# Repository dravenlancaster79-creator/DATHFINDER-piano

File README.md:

# DATHFINDER-piano
very simple begginer PCB that is a out of tune piano, with four different buttons having a different tone! i built this
 because i wanted to learn hoe PCBs work and operate, so far ive learned many new skills including Kcad and Cpp!!

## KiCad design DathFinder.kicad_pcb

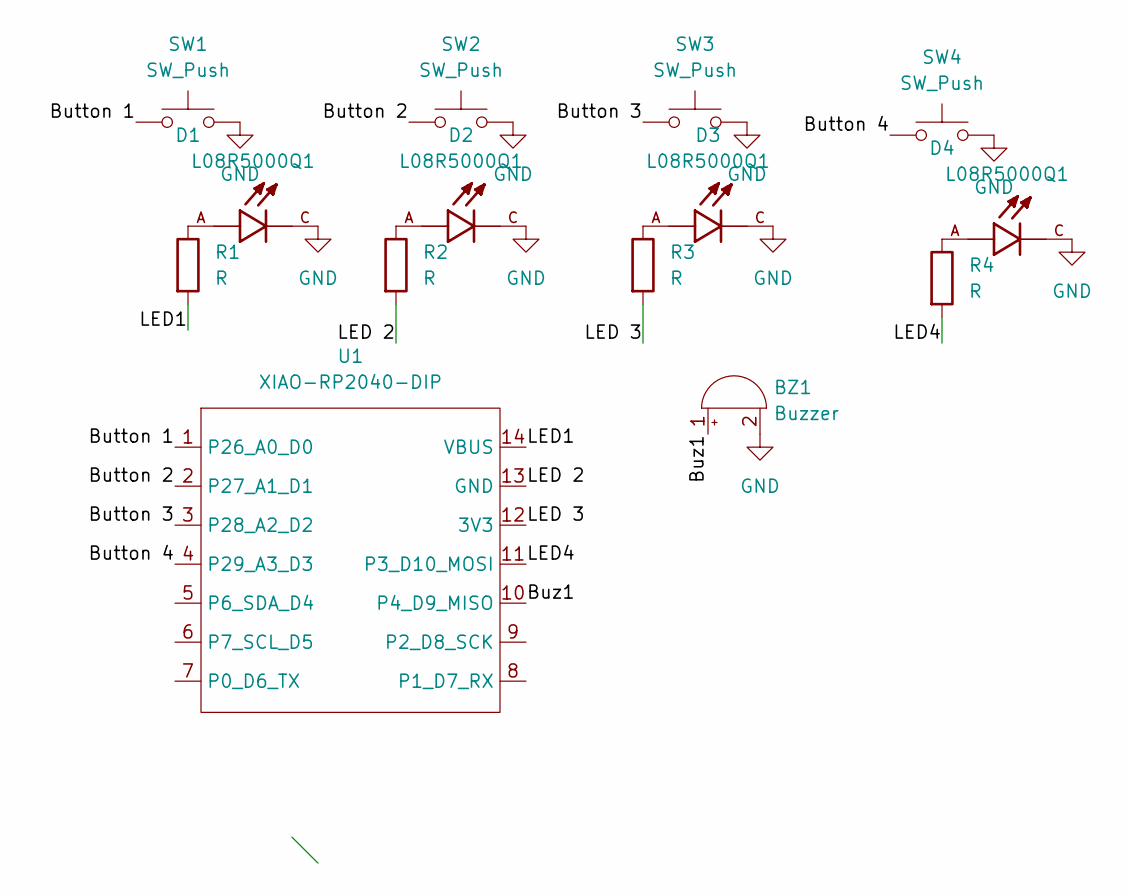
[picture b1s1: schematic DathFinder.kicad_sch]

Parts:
BZ1: Buzzer; Buzzer_D14mm_H7mm_P10mm
D1, D2, D3, D4: L08R5000Q1; LEDRD254W57D500H1070; PARTREV NA
R1, R2, R3, R4: R; R_Axial_DIN0204_L3.6mm_D1.6mm_P5.08mm_Horizontal
SW1, SW2, SW3, SW4: SW_Push; SW_Cherry_MX_1.00u_Plate
U1: XIAO-RP2040-DIP

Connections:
/Button 1: SW1.1, U1.1 (P26_A0_D0)
/Button 2: SW2.1, U1.2 (P27_A1_D1)
/Button 3: SW3.1, U1.3 (P28_A2_D2)
/Button 4: SW4.1, U1.4 (P29_A3_D3)
/Buz1: BZ1.1 (+), U1.10 (P4_D9_MISO)
/LED1: R1.2, U1.14 (VBUS)
/LED4: R4.2, U1.11 (P3_D10_MOSI)
/LED 2: R2.2, U1.13 (GND)
/LED 3: R3.2, U1.12 (3V3)
GND: BZ1.2 (-), D1.C, D2.C, D3.C, D4.C, SW1.2, SW2.2, SW3.2, SW4.2
unnamed: D1.A, R1.1
unnamed: D2.A, R2.1
unnamed: D3.A, R3.1
unnamed: D4.A, R4.1

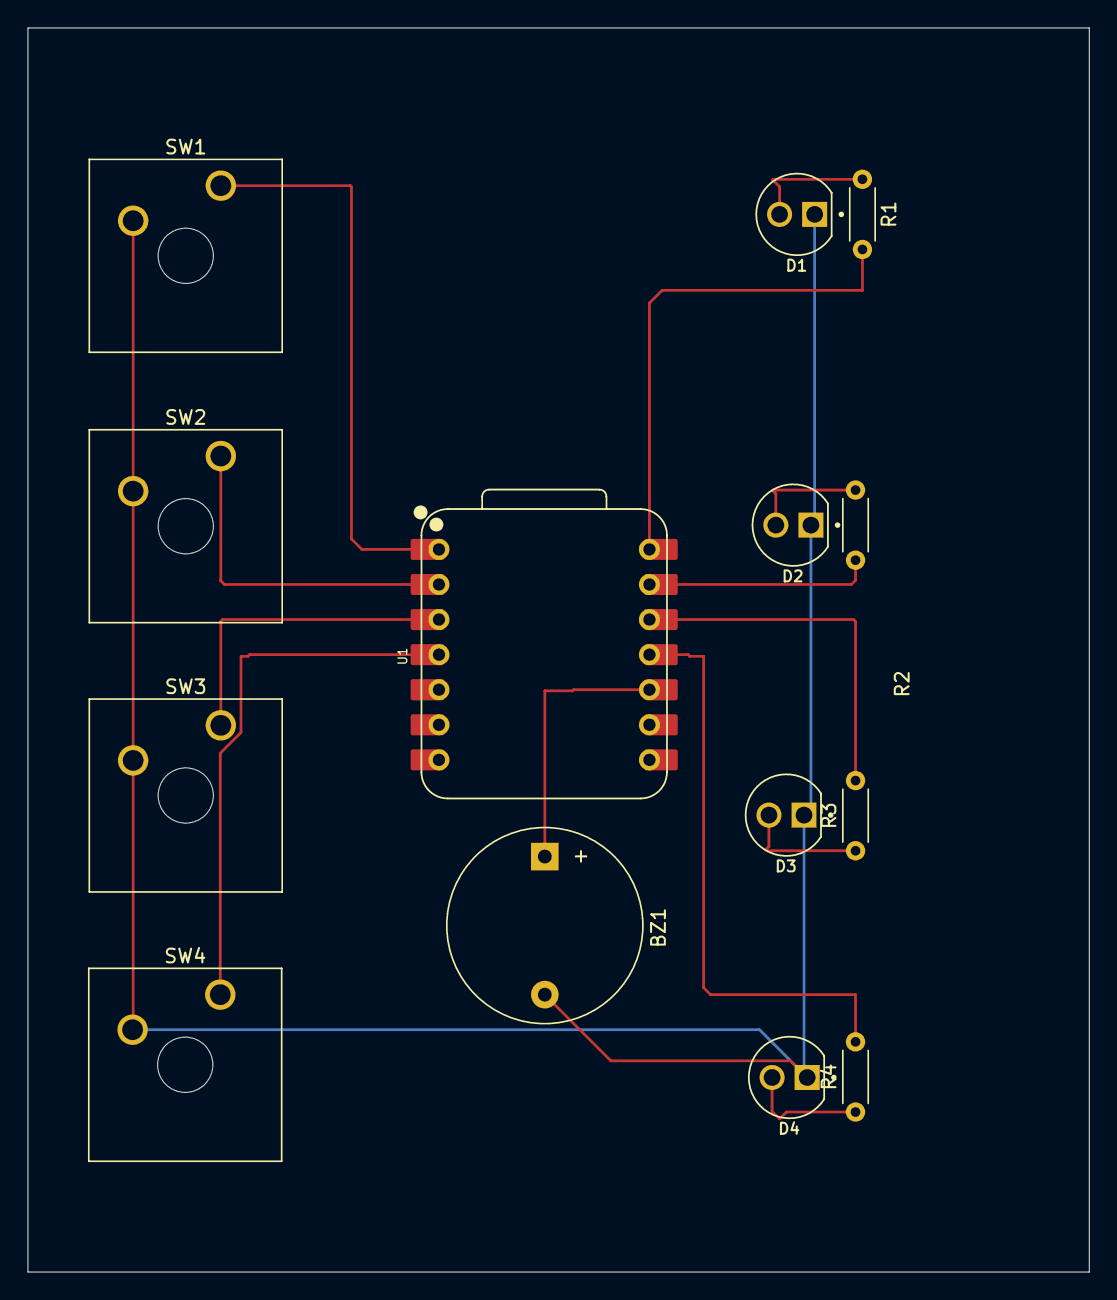
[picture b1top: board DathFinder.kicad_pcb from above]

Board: 2 copper layers, 76.9 x 90.1 mm, 14 parts (0 on the bottom side), 14 nets.

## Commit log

2026-06-12 Add images to README for DATHFINDER-piano
    Added multiple images showcasing the DATHFINDER-piano project.
2026-06-12 Remove an image from README.md
    Removed an image from the README file.
2026-06-13 Enhance README with project learning insights
    Expanded the project description to include learning experiences with PCBs and software.
